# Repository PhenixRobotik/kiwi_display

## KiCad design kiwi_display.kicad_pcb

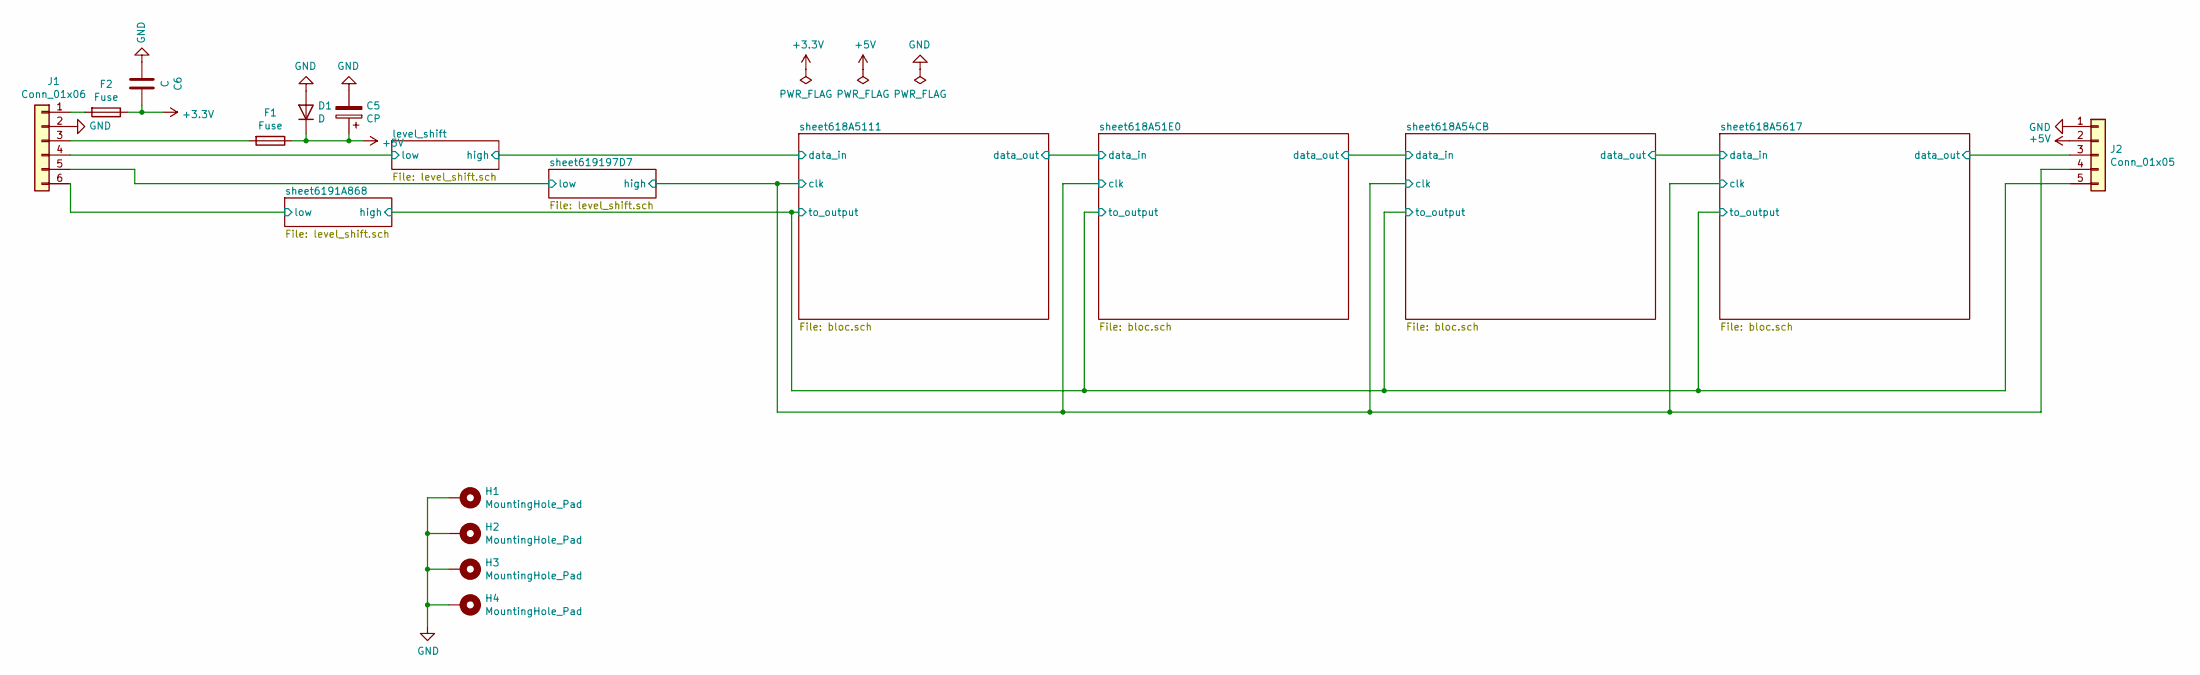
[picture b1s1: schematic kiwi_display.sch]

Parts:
C5: CP; CP_Radial_D5.0mm_P2.00mm
C6: C; C_0805_2012Metric_Pad1.18x1.45mm_HandSolder
D1: D; D_DO-35_SOD27_P10.16mm_Horizontal
F1, F2: Fuse; Fuse_1206_3216Metric_Pad1.42x1.75mm_HandSolder
H1, H2, H3, H4: MountingHole_Pad; MountingHole_3.2mm_M3_DIN965_Pad
J1: Conn_01x06; JST_PH_B6B-PH-K_1x06_P2.00mm_Vertical
J2: Conn_01x05; JST_PH_B5B-PH-K_1x05_P2.00mm_Vertical

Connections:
+3V3: C6.1, F2.1; also elsewhere on the board
+5V: C5.1, D1.1 (K), F1.1, J2.2; also elsewhere on the board
/level_shift/low: J1.4; also elsewhere on the board
/sheet618A5111/clk: J2.4; also elsewhere on the board
/sheet618A5617/data_out: J2.3; also elsewhere on the board
/sheet6191A868/high: J2.5; also elsewhere on the board
/sheet6191A868/low: J1.6; also elsewhere on the board
/sheet619197D7/low: J1.5; also elsewhere on the board
GND: C5.2, C6.2, D1.2 (A), H1.1, H2.1, H3.1, H4.1, J1.2, J2.1; also elsewhere on the board
unnamed: F1.2, J1.3
unnamed: F2.2, J1.1

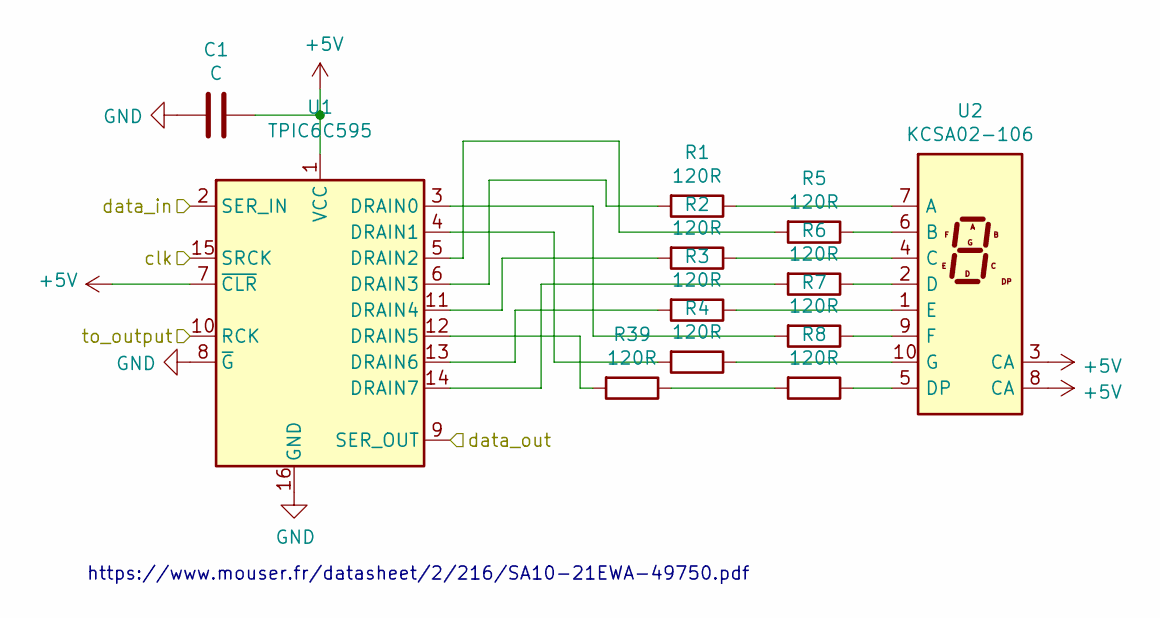
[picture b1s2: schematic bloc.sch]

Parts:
C1: C; C_0805_2012Metric_Pad1.18x1.45mm_HandSolder
R1, R2, R3, R4, R5, R6, R7, R8, R39: 120R; R_0805_2012Metric_Pad1.20x1.40mm_HandSolder
U1: TPIC6C595; DIP-16_W7.62mm
U2: KCSA02-106; 7seg

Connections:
+5V: C1.1, U1.1 (VCC), U1.7 (~CLR), U2.3 (CA), U2.8 (CA); also elsewhere on the board
/sheet618A51E0/data_in: U1.9 (SER_OUT); also elsewhere on the board
/sheet618A5111/clk: U1.15 (SRCK); also elsewhere on the board
/sheet618A5111/data_in: U1.2 (SER_IN); also elsewhere on the board
/sheet6191A868/high: U1.10 (RCK); also elsewhere on the board
GND: C1.2, U1.8 (~G), U1.16 (GND); also elsewhere on the board
unnamed: R1.1, U2.7 (A)
unnamed: R1.2, U1.6 (DRAIN3)
unnamed: R2.1, U2.4 (C)
unnamed: R2.2, U1.11 (DRAIN4)
unnamed: R3.1, U2.1 (E)
unnamed: R3.2, U1.13 (DRAIN6)
unnamed: R4.1, U2.10 (G)
unnamed: R4.2, U1.4 (DRAIN1)
unnamed: R5.1, U2.6 (B)
unnamed: R5.2, U1.5 (DRAIN2)
unnamed: R6.1, U2.2 (D)
unnamed: R6.2, U1.14 (DRAIN7)
unnamed: R7.1, U2.9 (F)
unnamed: R7.2, U1.3 (DRAIN0)
unnamed: R8.1, U2.5 (DP)
unnamed: R8.2, R39.1
unnamed: R39.2, U1.12 (DRAIN5)

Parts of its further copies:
C2, C3, C4: C; C_0805_2012Metric_Pad1.18x1.45mm_HandSolder
R9, R10, R11, R12, R13, R14, R15, R16, R17, R18, R19, R20, R21, R22, R23, R24, R25, R26, R27, R28, R29, R30, R31, R32, R40, R41, R42: 120R; R_0805_2012Metric_Pad1.20x1.40mm_HandSolder
U3, U5, U7: TPIC6C595; DIP-16_W7.62mm
U4, U6, U8: KCSA02-106; 7seg

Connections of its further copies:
+5V: C2.1, C3.1, C4.1, U3.1 (VCC), U3.7 (~CLR), U4.3 (CA), U4.8 (CA), U5.1 (VCC), U5.7 (~CLR), U6.3 (CA), U6.8 (CA), U7.1 (VCC), U7.7 (~CLR), U8.3 (CA), U8.8 (CA); also elsewhere on the board
/sheet618A51E0/data_in: U3.2 (SER_IN); also elsewhere on the board
/sheet618A54CB/data_in: U3.9 (SER_OUT), U5.2 (SER_IN)
/sheet618A5111/clk: U3.15 (SRCK), U5.15 (SRCK), U7.15 (SRCK); also elsewhere on the board
/sheet618A5617/data_in: U5.9 (SER_OUT), U7.2 (SER_IN)
/sheet618A5617/data_out: U7.9 (SER_OUT); also elsewhere on the board
/sheet6191A868/high: U3.10 (RCK), U5.10 (RCK), U7.10 (RCK); also elsewhere on the board
GND: C2.2, C3.2, C4.2, U3.8 (~G), U3.16 (GND), U5.8 (~G), U5.16 (GND), U7.8 (~G), U7.16 (GND); also elsewhere on the board
unnamed: R9.1, U4.7 (A)
unnamed: R9.2, U3.6 (DRAIN3)
unnamed: R10.1, U4.4 (C)
unnamed: R10.2, U3.11 (DRAIN4)
unnamed: R11.1, U4.1 (E)
unnamed: R11.2, U3.13 (DRAIN6)
unnamed: R12.1, U4.10 (G)
unnamed: R12.2, U3.4 (DRAIN1)
unnamed: R13.1, U4.6 (B)
unnamed: R13.2, U3.5 (DRAIN2)
unnamed: R14.1, U4.2 (D)
unnamed: R14.2, U3.14 (DRAIN7)
unnamed: R15.1, U4.9 (F)
unnamed: R15.2, U3.3 (DRAIN0)
unnamed: R16.1, U4.5 (DP)
unnamed: R16.2, R40.1
unnamed: R17.1, U6.7 (A)
unnamed: R17.2, U5.6 (DRAIN3)
unnamed: R18.1, U6.4 (C)
unnamed: R18.2, U5.11 (DRAIN4)
unnamed: R19.1, U6.1 (E)
unnamed: R19.2, U5.13 (DRAIN6)
unnamed: R20.1, U6.10 (G)
unnamed: R20.2, U5.4 (DRAIN1)
unnamed: R21.1, U6.6 (B)
unnamed: R21.2, U5.5 (DRAIN2)
unnamed: R22.1, U6.2 (D)
unnamed: R22.2, U5.14 (DRAIN7)
unnamed: R23.1, U6.9 (F)
unnamed: R23.2, U5.3 (DRAIN0)
unnamed: R24.1, U6.5 (DP)
unnamed: R24.2, R41.1
unnamed: R25.1, U8.7 (A)
unnamed: R25.2, U7.6 (DRAIN3)
unnamed: R26.1, U8.4 (C)
unnamed: R26.2, U7.11 (DRAIN4)
unnamed: R27.1, U8.1 (E)
unnamed: R27.2, U7.13 (DRAIN6)
unnamed: R28.1, U8.10 (G)
unnamed: R28.2, U7.4 (DRAIN1)
unnamed: R29.1, U8.6 (B)
unnamed: R29.2, U7.5 (DRAIN2)
unnamed: R30.1, U8.2 (D)
unnamed: R30.2, U7.14 (DRAIN7)
unnamed: R31.1, U8.9 (F)
unnamed: R31.2, U7.3 (DRAIN0)
unnamed: R32.1, U8.5 (DP)
unnamed: R32.2, R42.1
unnamed: R40.2, U3.12 (DRAIN5)
unnamed: R41.2, U5.12 (DRAIN5)
unnamed: R42.2, U7.12 (DRAIN5)

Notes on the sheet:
https://www.mouser.fr/datasheet/2/216/SA10-21EWA-49750.pdf

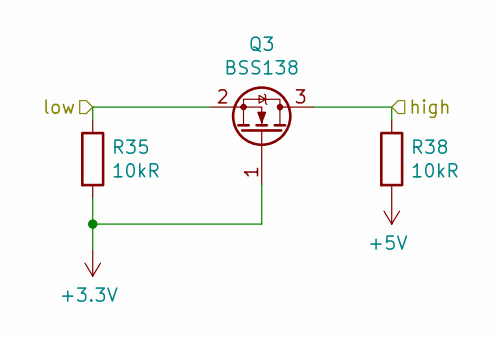
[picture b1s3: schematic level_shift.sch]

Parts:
Q1: BSS138; SOT-23
R36, R37: 10kR; R_0805_2012Metric_Pad1.20x1.40mm_HandSolder

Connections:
+3V3: Q1.1 (G), R36.2; also elsewhere on the board
+5V: R37.2; also elsewhere on the board
/level_shift/low: Q1.2 (S), R36.1; also elsewhere on the board
/sheet618A5111/data_in: Q1.3 (D), R37.1; also elsewhere on the board

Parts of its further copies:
Q2, Q3: BSS138; SOT-23
R33, R34, R35, R38: 10kR; R_0805_2012Metric_Pad1.20x1.40mm_HandSolder

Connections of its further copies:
+3V3: Q2.1 (G), Q3.1 (G), R33.2, R35.2; also elsewhere on the board
+5V: R34.2, R38.2; also elsewhere on the board
/sheet618A5111/clk: Q2.3 (D), R34.1; also elsewhere on the board
/sheet6191A868/high: Q3.3 (D), R38.1; also elsewhere on the board
/sheet6191A868/low: Q3.2 (S), R35.1; also elsewhere on the board
/sheet619197D7/low: Q2.2 (S), R33.1; also elsewhere on the board

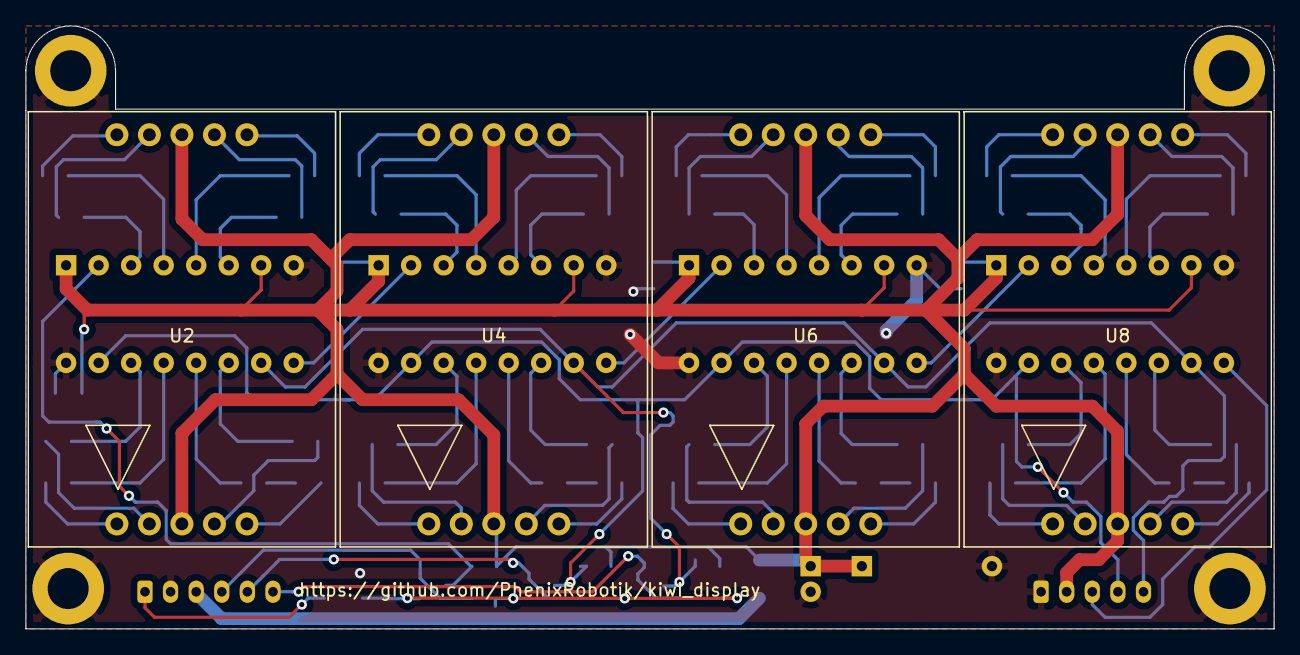
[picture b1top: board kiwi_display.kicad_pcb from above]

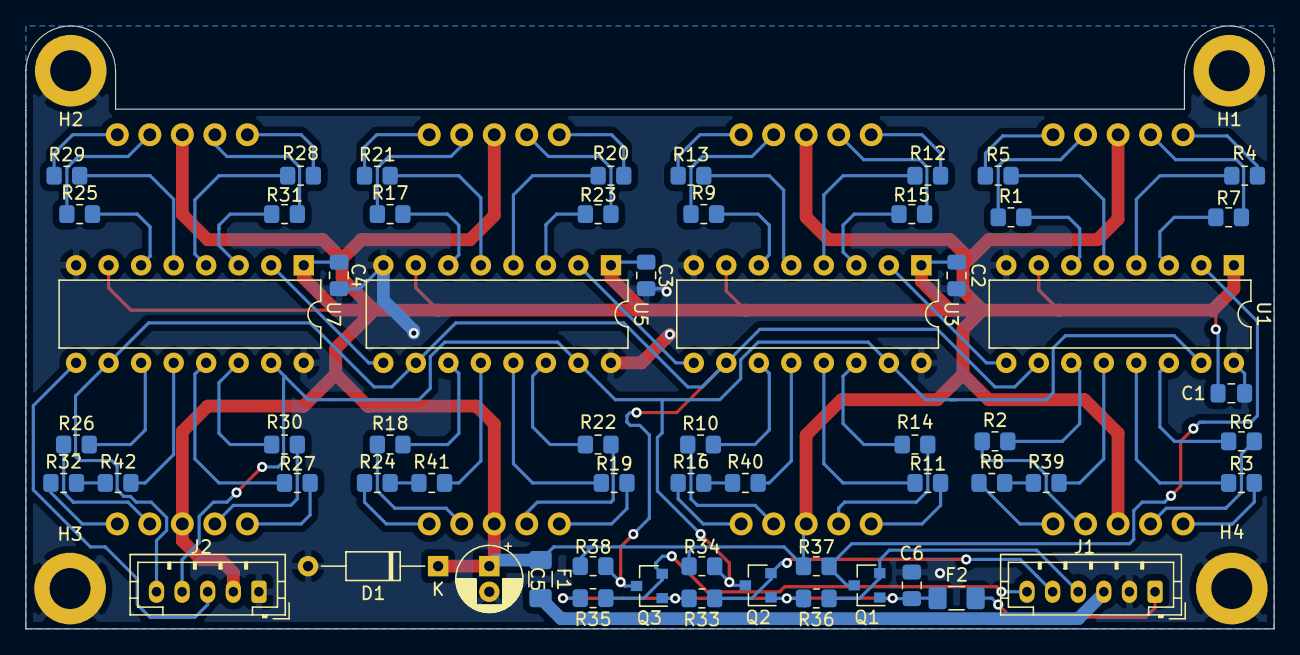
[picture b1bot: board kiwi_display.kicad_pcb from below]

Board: 2 copper layers, 97.5 x 47.1 mm, 68 parts (64 on the bottom side), 83 nets.

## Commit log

2021-11-08 full board
2021-12-03 with cms resistors
